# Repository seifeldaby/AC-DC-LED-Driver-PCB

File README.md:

# ⚡ AC-to-DC LED Driver PCB — Five-Channel Infrared LED Driver NOTE : photos under review

---

## 📋 Project Overview

This project is a **fully hand-fabricated AC-to-DC regulated power supply** designed to drive **five infrared LEDs** simultaneously. It was developed as part of the Electrical & Electronics Engineering curriculum at **Assiut University**, under the supervision of **Dr. Khalil Ismail**.

The circuit converts a **17 V peak / 50 Hz sinusoidal AC** input into a stable **9.1 V regulated DC output** using a Zener shunt regulator, and distributes ~18.8 mA to each of the five IR LED branches.

---

## 🧩 Circuit Architecture

The circuit is structured as a cascade of four functional stages:

```
AC Input → Full-Wave Bridge Rectifier → Capacitive Filter → Zener Regulator → 5× LED Branches
```

| Stage | Component | Value / Part |
|-------|-----------|-------------|
| AC Input | Terminal Block (TB1) | 2-Pin, 5.08 mm pitch |
| Rectifier | D1–D4 | 1N4007 (×4) |
| Filter | C1 | 2200 µF / 50 V Electrolytic |
| Pre-reg Resistor | R1 | 47 Ω, ≥ 1 W |
| Zener Regulator | D5 | 1N4739A (9.1 V, 1 W) |
| LED Resistors | R2–R6 | 420 Ω, ¼ W (×5) |
| LEDs | LED1–LED5 | Infrared LEDs (Vf ≈ 1.2 V) |

---

## 📐 Key Design Calculations

| Parameter | Value |
|-----------|-------|
| AC Peak Voltage | 17 V |
| AC RMS Voltage | 12.02 V |
| Peak Voltage After Rectifier | 15.6 V |
| Ripple Voltage (p-p) | ~0.2 V |
| Regulated Output (Zener) | 9.1 V |
| Current Through R1 | ~134 mA |
| Zener Current (max) | ~90 mA |
| Zener Power Dissipation (max) | ~0.82 W |
| Current Per LED Branch | ~18.8 mA |
| Total LED Current | ~94 mA |

---

## 🖥️ Step 1 — Schematic Design in LTspice

The circuit was first drawn and simulated in **LTspice** using a `.tran 0.5` transient analysis (500 ms window) to verify rectification, filtering, and regulation behaviour before committing to PCB layout.

<p align="center">
  
  <br><em>Figure 1 — LTspice Schematic</em>
</p>

### Simulation Waveforms

**Rectified & Filtered DC Voltage (V_cap):**

<p align="center">
  
  <br><em>Figure 2 — V_cap: Pulsating DC before regulation (~15.4 V with 0.2 V ripple)</em>
</p>

**Regulated Zener Output (9.1 V):**

<p align="center">
  
  <br><em>Figure 3 — Stable 9.1 V regulated output</em>
</p>

---

## 🖨️ Step 2 — PCB Design in KiCad

After successful simulation, the schematic was transferred to **KiCad** for PCB layout. Key design decisions included:

- AC input traces routed with **≥ 2 mm creepage/clearance** from DC traces (per IEC 60950)
- Zener diode and R1 placed close together to **minimise high-current trace length**
- LED resistors (R2–R6) arranged in a **symmetrical column** matching LED positions
- Terminal block mounted at **board edge** for direct cable access
- All components on the **top layer**; solder joints on the **bottom layer**

<p align="center">
  
  <br><em>Figure 5 — Schematic captured in KiCad</em>
</p>

<p align="center">
  
  <br><em>Figure 6 — PCB Top Layer Layout</em>
</p>

<p align="center">
  
  <br><em>Figure 7 — PCB 3D Render (Top View)</em>
</p>

---

## 🏭 Step 3 — PCB Manual Fabrication

The board was fabricated entirely by hand using the **toner transfer method**. Below is the complete process:

### 3.1 Toner Transfer

The layout was printed on **glossy paper** using a laser printer, then heat-transferred onto the copper-clad board using an iron.

<p align="center">
  
  <br><em>Figure 8 — Toner transferred onto copper-clad board</em>
</p>

### 3.2 Chemical Etching

The board was submerged in **Ferric Chloride (FeCl₃)** solution to dissolve the exposed copper, leaving only the toner-protected traces.

<p align="center">
  
  <br><em>Figure 9 — Board during chemical etching process</em>
</p>

### 3.3 Cleaning & Inspection

Toner was removed with **Acetone/Thinner** to reveal the copper tracks. A visual inspection was performed to check for shorts or broken traces.

<p align="center">
  
  <br><em>Figure 10 — Board after cleaning, copper traces visible</em>
</p>

### 3.4 Continuity Testing

A **Digital Multimeter** was used to verify electrical integrity of all traces before drilling.

<p align="center">
  
  <br><em>Figure 11 — Continuity testing with DMM</em>
</p>

### 3.5 Drilling

Precision holes were drilled using a **mini drill press** with bit sizes of **0.8 mm – 1.0 mm** depending on component lead diameter.

<p align="center">
  
  <br><em>Figure 12 — Drilling through-hole component pads</em>
</p>

### 3.6 Component Assembly & Soldering

Components were placed per the silkscreen layout and soldered using a **temperature-controlled iron** with lead-tin wire, targeting concave solder joints for maximum reliability.
</p>
<p align="center">
  
  <br><em>Figure 13 — Components being assempled onto the board</em>
</p>
<p align="center">
  
  <br><em>Figure 13 — Components being soldered onto the board</em>
</p>
<p align="center">
  
  <br><em>Figure 13 — Components being soldered onto the board</em>

---

## ✅ Step 4 — Testing & Verification

After assembly, the circuit was powered through a **safety isolation transformer** for the initial power-up. Output voltage and LED branch currents were measured with a multimeter to confirm they met specifications.

<p align="center">
  
  <br><em>Figure 14 — Measuring output voltage and current </em>
</p>

---

## 🎉 Final Result

The completed board with all five IR LEDs operational:

<p align="center">
  
  <br><em>Figure 15 — Final assembled board with LEDs powered on</em>
</p>

The board was then cleaned with **Isopropyl Alcohol (IPA)** to remove flux residues.

---

## 🔬 Results Summary

| Measurement | Expected | Result |
|-------------|----------|--------|
| Regulated Output Voltage | 9.1 V | ✅ 9.1 V |
| LED Branch Current | ~18.8 mA | ✅ Within spec |
| Ripple Voltage | ~0.2 V p-p | ✅ Well-smoothed |
| Zener Power Dissipation | ≤ 1 W | ✅ ~0.82 W max |
| All LEDs Operational | 5/5 | ✅ 5/5 |

---

## 🛠️ Tools Used

| Tool | Purpose |
|------|---------|
| **LTspice** | Circuit simulation & waveform analysis |
| **KiCad** | Schematic capture & PCB layout |
| **Ferric Chloride** | Chemical etching |
| **Soldering Iron** | Component assembly |
| **Digital Multimeter** | Continuity testing & measurements |

---

## 📁 Repository Structure

```
📦 AC-DC-LED-Driver-PCB
 ┣ 📂 images/                  ← All photos and screenshots
 ┣ 📂 ltspice/                 ← LTspice simulation files 
 ┣ 📂 kicad/                   ← KiCad project files 
 ┣ 📄 README.md                ← This file
 ┗ 📄 LED_Driver_PCB_Report.pdf ← Full technical report
```

---

## 👤 Author

**Seif Elden Mostafa Salah Eldaby**  
Electrical & Electronics Engineering — Assiut University (Class of 2029)  

**Supervisor:** Dr. Khalil Ismail  
Faculty of Engineering — Assiut University

---

## 📄 License

This project is submitted as academic work at Assiut University. Feel free to use it for learning purposes with proper attribution.

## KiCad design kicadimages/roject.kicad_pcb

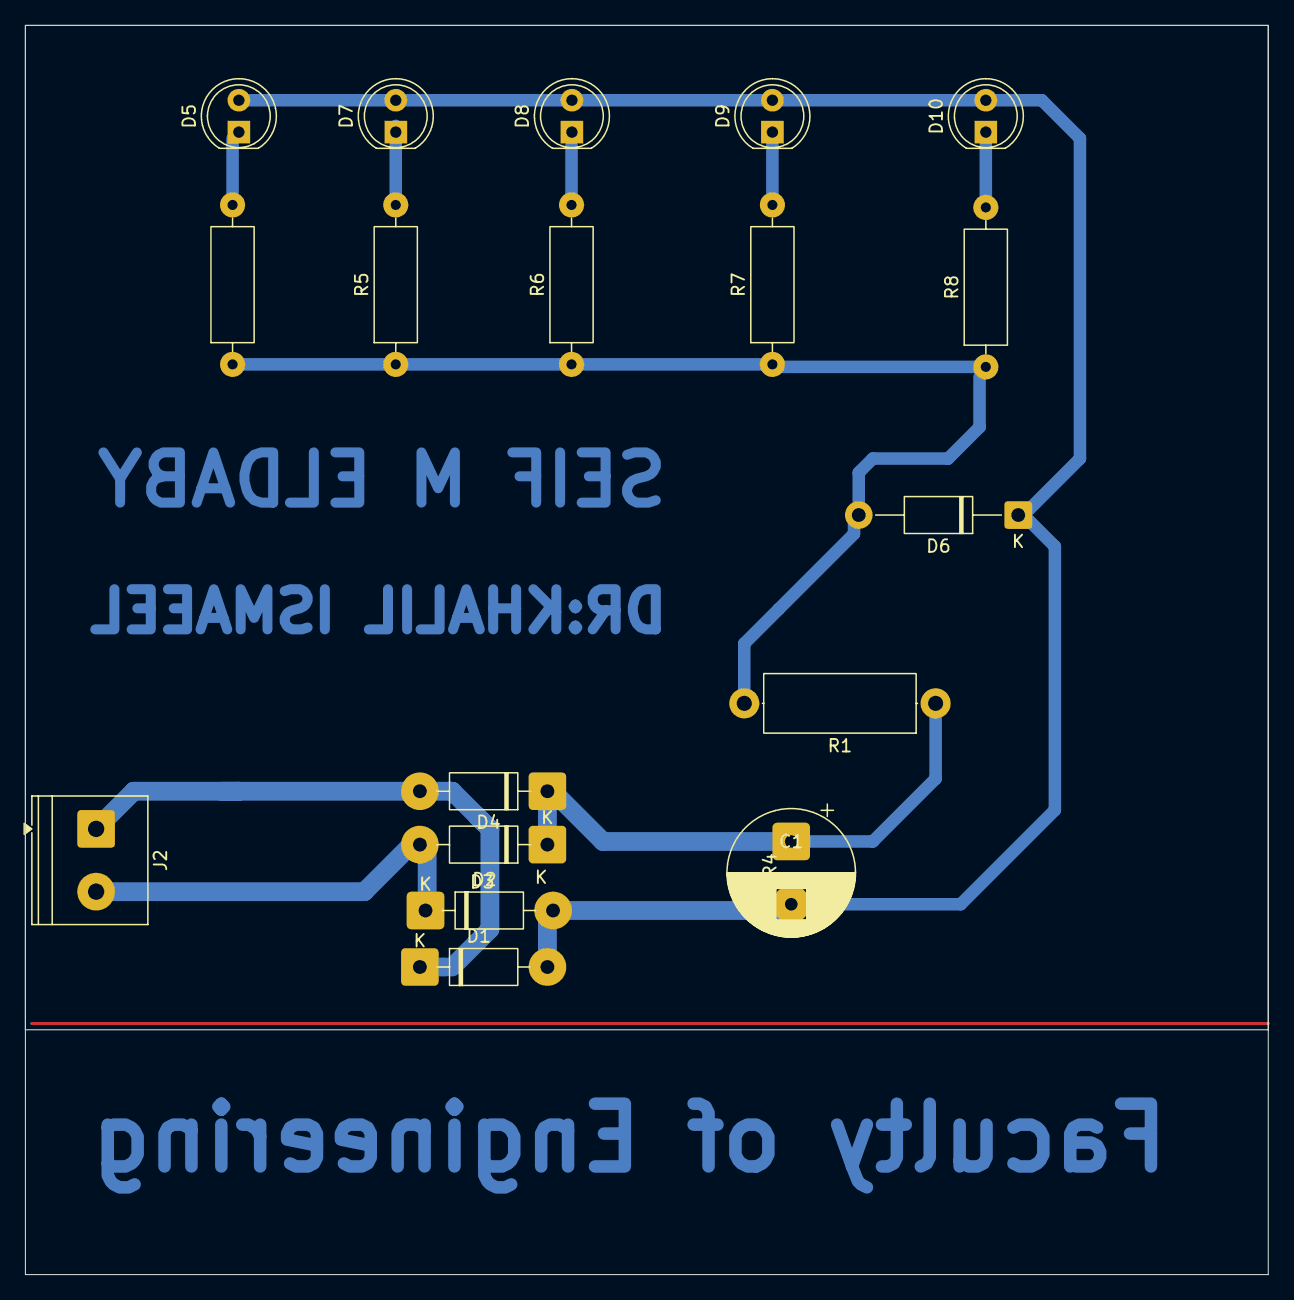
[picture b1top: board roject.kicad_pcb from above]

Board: 2 copper layers, 99.0 x 99.5 mm, 18 parts (0 on the bottom side), 8 nets.

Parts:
C1: C_Polarized; CP_Radial_D10.0mm_P5.00mm
D1, D2, D3, D4: 1N4007; D_DO-41_SOD81_P10.16mm_Horizontal
D5, D7, D8, D9, D10: LED; LED_D5.0mm
D6: D_Zener; D_DO-41_SOD81_P12.70mm_Horizontal
J2: Screw_Terminal_01x02; TerminalBlock_Phoenix_PT-1,5-2-5.0-H_1x02_P5.00mm_Horizontal
R1: R; R_Axial_DIN0414_L11.9mm_D4.5mm_P15.24mm_Horizontal
R4, R5, R6, R7, R8: R; R_Axial_DIN0309_L9.0mm_D3.2mm_P12.70mm_Horizontal

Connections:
GND: C1.2, D1.2 (A), D3.2 (A), D6.2 (A), R4.1, R5.1, R6.1
unnamed: D1.1 (K), D2.2 (A)
unnamed: C1.1, D2.1 (K), D4.1 (K), R1.1, R7.1, R8.1
unnamed: D3.1 (K), D4.2 (A), J2.1
unnamed: D5.1 (K), R5.2
unnamed: D7.1 (K), R4.2
unnamed: D5.2 (A), D6.1 (K), D7.2 (A), D8.2 (A), D9.2 (A), D10.2 (A), J2.2, R1.2, R7.2, R8.2
unnamed: D10.1 (K), R6.2

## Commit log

2026-04-28 Revise README for AC-to-DC LED Driver project
    Updated the README to provide a detailed project overview, circuit architecture, design calculations, and fabrication steps for the AC-to-DC LED Driver PCB.
2026-04-28 Fix image references and update formats in README
    Updated image file formats and corrected references in the README.
2026-04-28 Fix image format and update figure caption
    Updated image file extension from .jpg to .jpeg and modified figure caption for clarity.
2026-04-28 Create ltspice
2026-04-28 Update directory descriptions in README
    Removed file extensions from directory descriptions in README.
